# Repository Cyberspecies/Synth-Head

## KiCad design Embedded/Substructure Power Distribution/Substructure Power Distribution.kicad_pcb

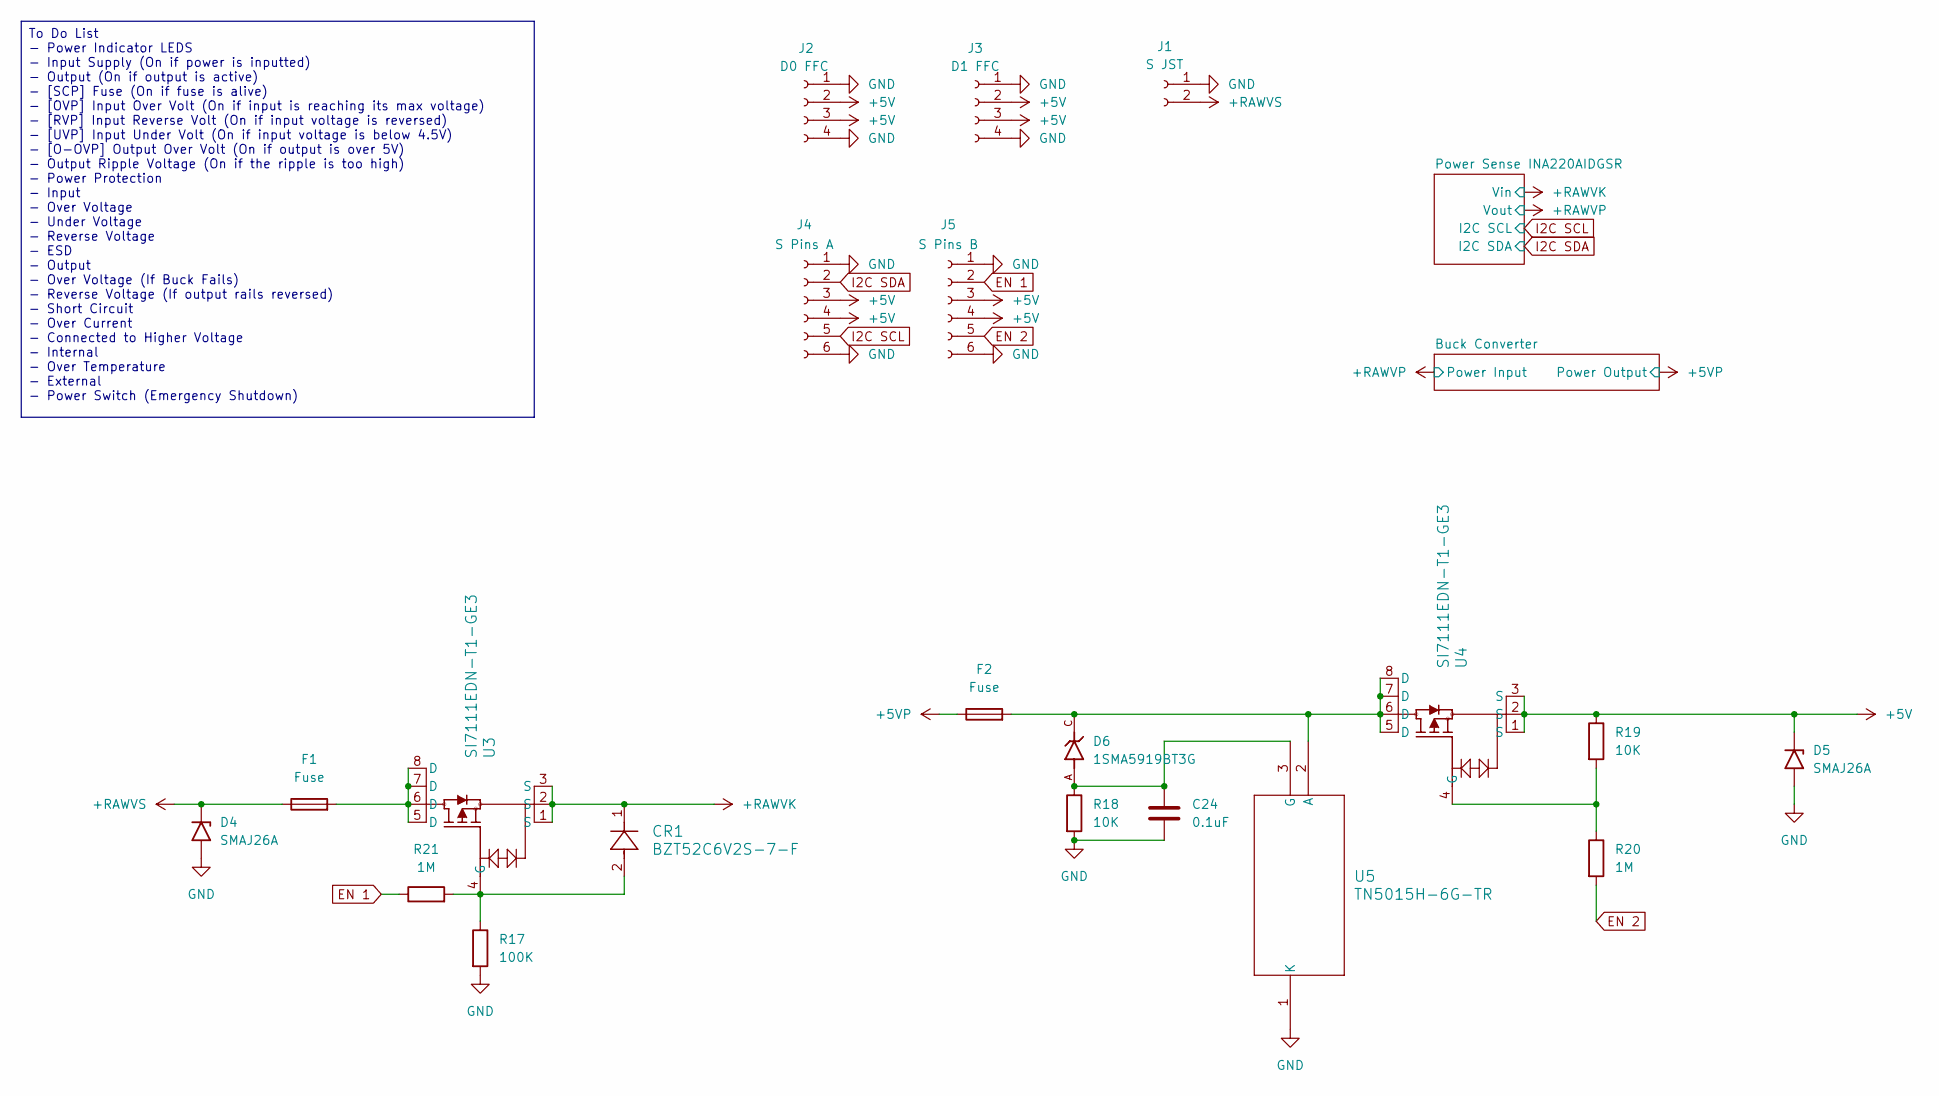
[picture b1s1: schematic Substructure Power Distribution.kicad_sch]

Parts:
C24: 0.1uF; C_0603_1608Metric_Pad1.08x0.95mm_HandSolder
CR1: BZT52C6V2S-7-F; SOD323_DIO
D4, D5: SMAJ26A; D_SMA
D6: 1SMA5919BT3G; DIOM5226X220N; PARTREV 10
F1, F2: Fuse; Fuse_1206_3216Metric_Pad1.42x1.75mm_HandSolder; LCSC C126815
J1: S JST; AMASS_XT30PW-M_1x02_P2.50mm_Horizontal
J2: D0 FFC; JST_XH_B4B-XH-A_1x04_P2.50mm_Vertical
J3: D1 FFC; JST_XH_B4B-XH-A_1x04_P2.50mm_Vertical
J4: S Pins A; PinHeader_1x06_P2.54mm_Vertical
J5: S Pins B; PinHeader_1x06_P2.54mm_Vertical
R17: 100K; R_0603_1608Metric_Pad0.98x0.95mm_HandSolder
R18, R19: 10K; R_0603_1608Metric_Pad0.98x0.95mm_HandSolder
R20, R21: 1M; R_0603_1608Metric_Pad0.98x0.95mm_HandSolder
U3, U4: SI7111EDN-T1-GE3; MOSFET_0DN-T1-GE3_VIS
U5: TN5015H-6G-TR; D2PAK_T2550_STM-M

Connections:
+5V: D5.1 (A1), J2.2, J2.3, J3.2, J3.3, J4.3, J4.4, J5.3, J5.4, R19.1, U4.1 (S), U4.2 (S), U4.3 (S)
+5VP: F2.1; also elsewhere on the board
+RAWVK: CR1.1, U3.1 (S), U3.2 (S), U3.3 (S); also elsewhere on the board
+RAWVS: D4.1 (A1), F1.1, J1.2
EN 1: J5.2, R21.1
EN 2: J5.5, R20.2
GND: C24.2, D4.2 (A2), D5.2 (A2), J1.1, J2.1, J2.4, J3.1, J3.4, J4.1, J4.6, J5.1, J5.6, R17.2, R18.2, U5.1 (K); also elsewhere on the board
I2C SCL: J4.5; also elsewhere on the board
I2C SDA: J4.2; also elsewhere on the board
unnamed: F1.2, U3.5 (D), U3.6 (D), U3.7 (D), U3.8 (D)
unnamed: CR1.2, R17.1, R21.2, U3.4 (G)
unnamed: R19.2, R20.1, U4.4 (G)
unnamed: D6.C, F2.2, U4.5 (D), U4.6 (D), U4.7 (D), U4.8 (D), U5.2 (A)
unnamed: C24.1, D6.A, R18.1, U5.3 (G)

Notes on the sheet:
To Do List - Power Indicator LEDS - Input Supply (On if power is inputted) - Output (On if output is active) - [SCP] Fuse (On if fuse is alive) - [OVP] Input Over Volt (On if input is reaching its max voltage) - [RVP] Input Reverse Volt (On if input voltage is reversed) - [UVP] Input Under Volt (On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

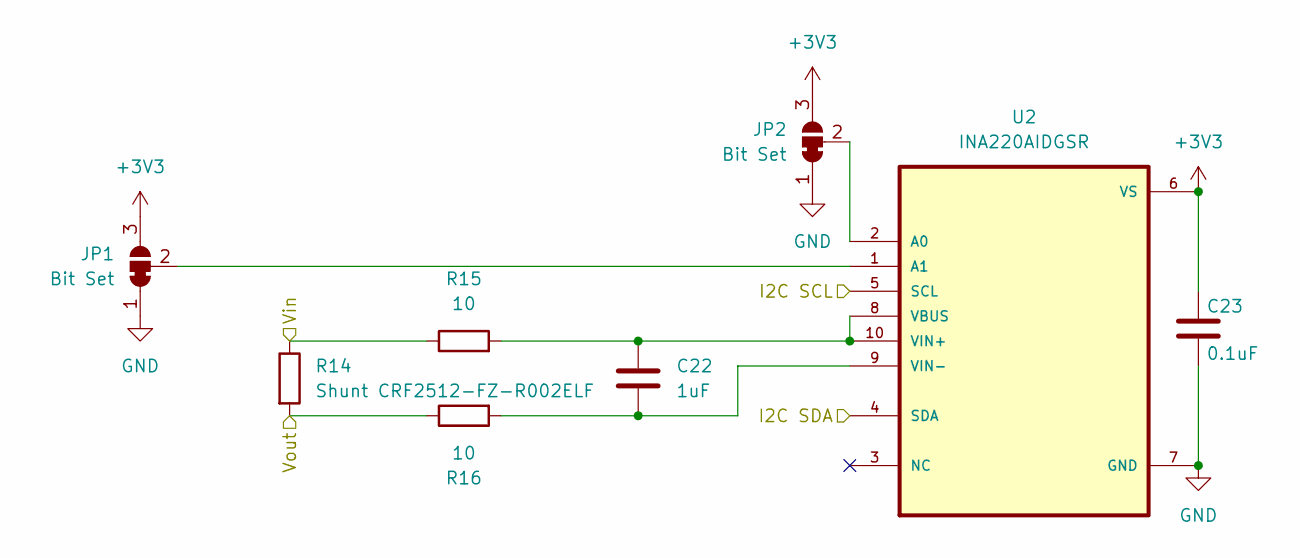
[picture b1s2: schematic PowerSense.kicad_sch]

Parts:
C22: 1uF; C_0402_1005Metric_Pad0.74x0.62mm_HandSolder
C23: 0.1uF; C_0402_1005Metric_Pad0.74x0.62mm_HandSolder
JP1, JP2: Bit Set; SolderJumper-3_P1.3mm_Bridged2Bar12_RoundedPad1.0x1.5mm
R14: Shunt CRF2512-FZ-R002ELF; R_2512_6332Metric_Pad1.40x3.35mm_HandSolder
R15, R16: 10; R_0402_1005Metric_Pad0.72x0.64mm_HandSolder
U2: INA220AIDGSR; SOP50P490X110-10N

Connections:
+3V3: C23.1, JP1.3 (B), JP2.3 (B), U2.6 (VS)
+RAWVK: R14.1, R15.1; also elsewhere on the board
+RAWVP: R14.2, R16.1; also elsewhere on the board
GND: C23.2, JP1.1 (A), JP2.1 (A), U2.7 (GND); also elsewhere on the board
I2C SCL: U2.5 (SCL); also elsewhere on the board
I2C SDA: U2.4 (SDA); also elsewhere on the board
unnamed: JP1.2 (C), U2.1 (A1)
unnamed: JP2.2 (C), U2.2 (A0)
unnamed: C22.1, R15.2, U2.8 (VBUS), U2.10 (VIN+)
unnamed: C22.2, R16.2, U2.9 (VIN-)

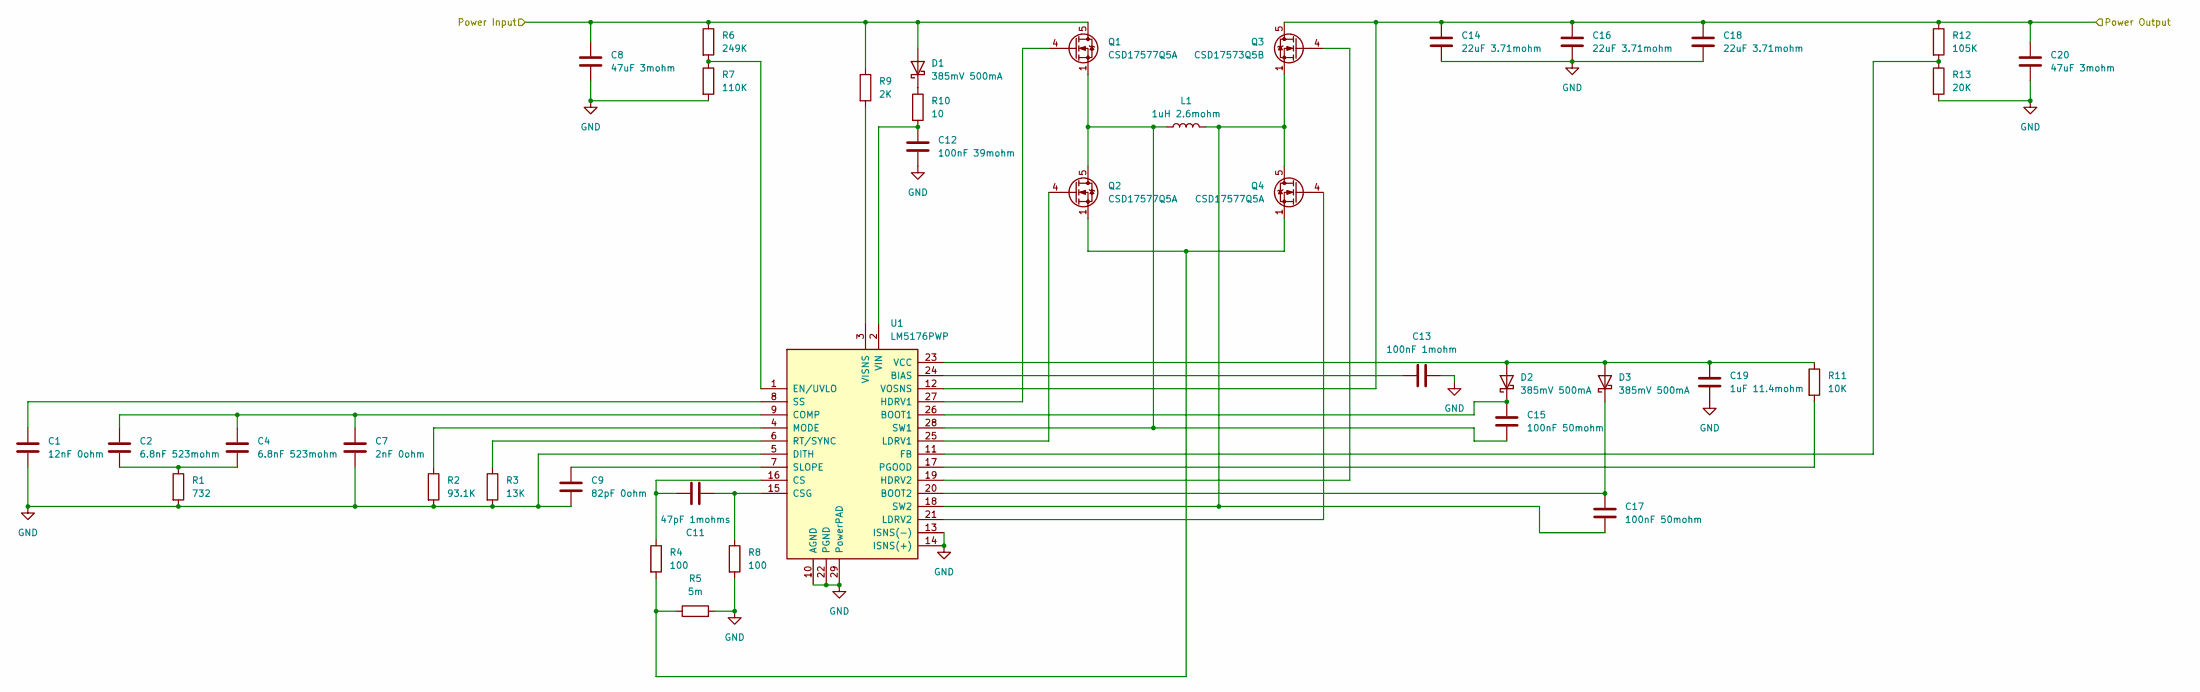
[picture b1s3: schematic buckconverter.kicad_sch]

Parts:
C1: 12nF 0ohm; C_0603_1608Metric_Pad1.08x0.95mm_HandSolder; LCSC C519540
C2, C4: 6.8nF 523mohm; C_0402_1005Metric_Pad0.74x0.62mm_HandSolder; LCSC C3840335
C7: 2nF 0ohm; C_0402_1005Metric_Pad0.74x0.62mm_HandSolder; LCSC C1845704
C8, C20: 47uF 3mohm; C_1210_3225Metric_Pad1.33x2.70mm_HandSolder; LCSC C77101
C9: 82pF 0ohm; C_0402_1005Metric_Pad0.74x0.62mm_HandSolder; LCSC C650992
C11: 47pF 1mohms; C_0402_1005Metric_Pad0.74x0.62mm_HandSolder; LCSC C76970
C12: 100nF 39mohm; R_0402_1005Metric_Pad0.72x0.64mm_HandSolder; LCSC C2181865
C13: 100nF 1mohm; C_0402_1005Metric_Pad0.74x0.62mm_HandSolder; LCSC C133086
C14, C16, C18: 22uF 3.71mohm; C_0603_1608Metric_Pad1.08x0.95mm_HandSolder; LCSC C86295
C15, C17: 100nF 50mohm; C_0603_1608Metric_Pad1.08x0.95mm_HandSolder; LCSC C92490
C19: 1uF 11.4mohm; C_0402_1005Metric_Pad0.74x0.62mm_HandSolder; LCSC C181015
D1: 385mV 500mA; D_SOD-123; LCSC C155367
D2, D3: 385mV 500mA; D_SOD-123; LCSC C398783
L1: 1uH 2.6mohm; XAL7070-102ME; LCSC C6609502
Q1, Q2, Q4: CSD17577Q5A; TDSON-8-1; LCSC C475504
Q3: CSD17573Q5B; TDSON-8-1; LCSC C202231
R1: 732; R_0402_1005Metric_Pad0.72x0.64mm_HandSolder; LCSC C2085222
R2: 93.1K; R_0402_1005Metric_Pad0.72x0.64mm_HandSolder; LCSC C2085865
R3: 13K; R_0402_1005Metric_Pad0.72x0.64mm_HandSolder; LCSC C294438
R4, R8: 100; R_0402_1005Metric_Pad0.72x0.64mm_HandSolder; LCSC C844713
R5: 5m; R_2512_6332Metric_Pad1.40x3.35mm_HandSolder; LCSC C22468851
R6: 249K; C_0402_1005Metric_Pad0.74x0.62mm_HandSolder; LCSC C482111
R7: 110K; C_0402_1005Metric_Pad0.74x0.62mm_HandSolder; LCSC C481928
R9: 2K; C_0402_1005Metric_Pad0.74x0.62mm_HandSolder; LCSC C482125
R10: 10; R_0402_1005Metric_Pad0.72x0.64mm_HandSolder; LCSC C481926
R11: 10K; R_0402_1005Metric_Pad0.72x0.64mm_HandSolder; LCSC C71617
R12: 105K; R_0603_1608Metric_Pad0.98x0.95mm_HandSolder; LCSC C227540
R13: 20K; R_0603_1608Metric_Pad0.98x0.95mm_HandSolder; LCSC C105575
U1: LM5176PWP; HTSSOP-28-1EP_4.4x9.7mm_P0.65mm_EP3.4x9.5mm_ThermalVias

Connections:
+5VP: C14.1, C16.1, C18.1, C20.1, Q3.5 (D), R12.1, U1.12 (VOSNS); also elsewhere on the board
+RAWVP: C8.1, D1.2 (A), Q1.5 (D), R6.1, R9.1; also elsewhere on the board
GND: C1.2, C7.2, C8.2, C9.2, C12.2, C13.2, C14.2, C16.2, C18.2, C19.2, C20.2, R1.2, R2.2, R3.2, R5.2, R7.2, R8.2, R13.2, U1.5 (DITH), U1.10 (AGND), U1.13 (ISNS(-)), U1.14 (ISNS(+)), U1.22 (PGND), U1.29 (PowerPAD); also elsewhere on the board
unnamed: C2.2, C4.2, R1.1
unnamed: D1.1 (K), R10.1
unnamed: C19.1, D2.2 (A), D3.2 (A), R11.1, U1.23 (VCC)
unnamed: C15.1, D2.1 (K), U1.26 (BOOT1)
unnamed: C17.1, D3.1 (K), U1.20 (BOOT2)
unnamed: Q1.4 (G), U1.27 (HDRV1)
unnamed: C15.2, L1.1, Q1.1 (S), Q1.2 (S), Q1.3 (S), Q2.5 (D), U1.28 (SW1)
unnamed: Q2.4 (G), U1.25 (LDRV1)
unnamed: Q2.1 (S), Q2.2 (S), Q2.3 (S), Q4.1 (S), Q4.2 (S), Q4.3 (S), R4.2, R5.1
unnamed: Q3.4 (G), U1.19 (HDRV2)
unnamed: C17.2, L1.2, Q3.1 (S), Q3.2 (S), Q3.3 (S), Q4.5 (D), U1.18 (SW2)
unnamed: Q4.4 (G), U1.21 (LDRV2)
unnamed: C13.1, U1.24 (BIAS)
unnamed: C2.1, C4.1, C7.1, U1.9 (COMP)
unnamed: C11.1, R4.1, U1.16 (CS)
unnamed: C11.2, R8.1, U1.15 (CSG)
unnamed: R6.2, R7.1, U1.1 (EN/UVLO)
unnamed: R12.2, R13.1, U1.11 (FB)
unnamed: R2.1, U1.4 (MODE)
unnamed: R11.2, U1.17 (PGOOD)
unnamed: R3.1, U1.6 (RT/SYNC)
unnamed: C9.1, U1.7 (SLOPE)
unnamed: C1.1, U1.8 (SS)
unnamed: C12.1, R10.2, U1.2 (VIN)
unnamed: R9.2, U1.3 (VISNS)

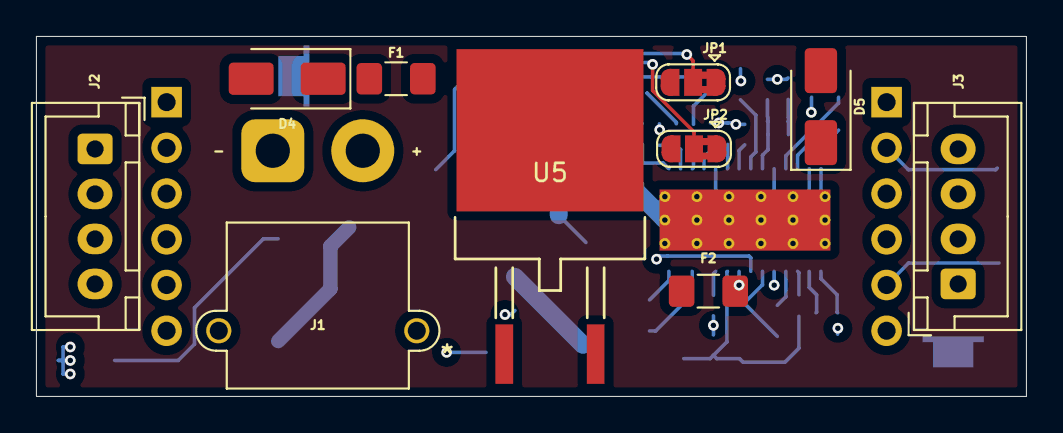
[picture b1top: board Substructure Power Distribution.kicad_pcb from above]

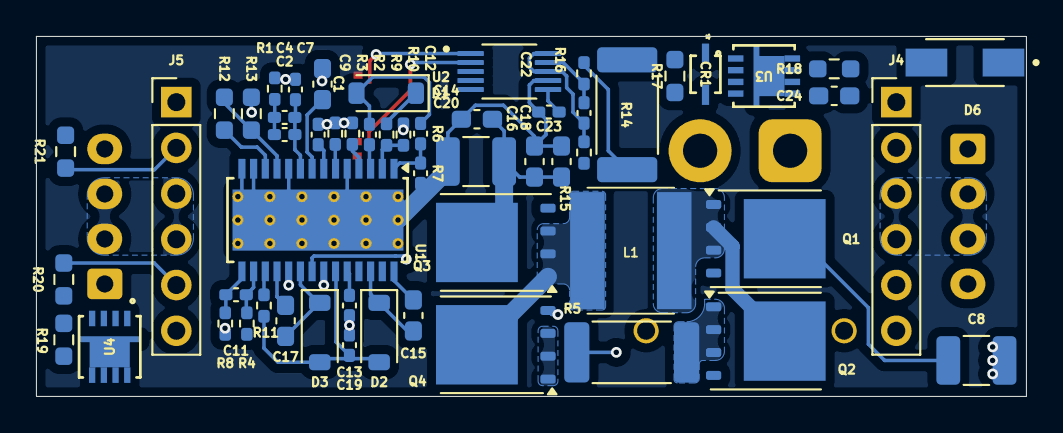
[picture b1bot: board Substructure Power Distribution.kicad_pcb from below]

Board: 4 copper layers, 55.0 x 20.0 mm, 66 parts (56 on the bottom side), 45 nets.

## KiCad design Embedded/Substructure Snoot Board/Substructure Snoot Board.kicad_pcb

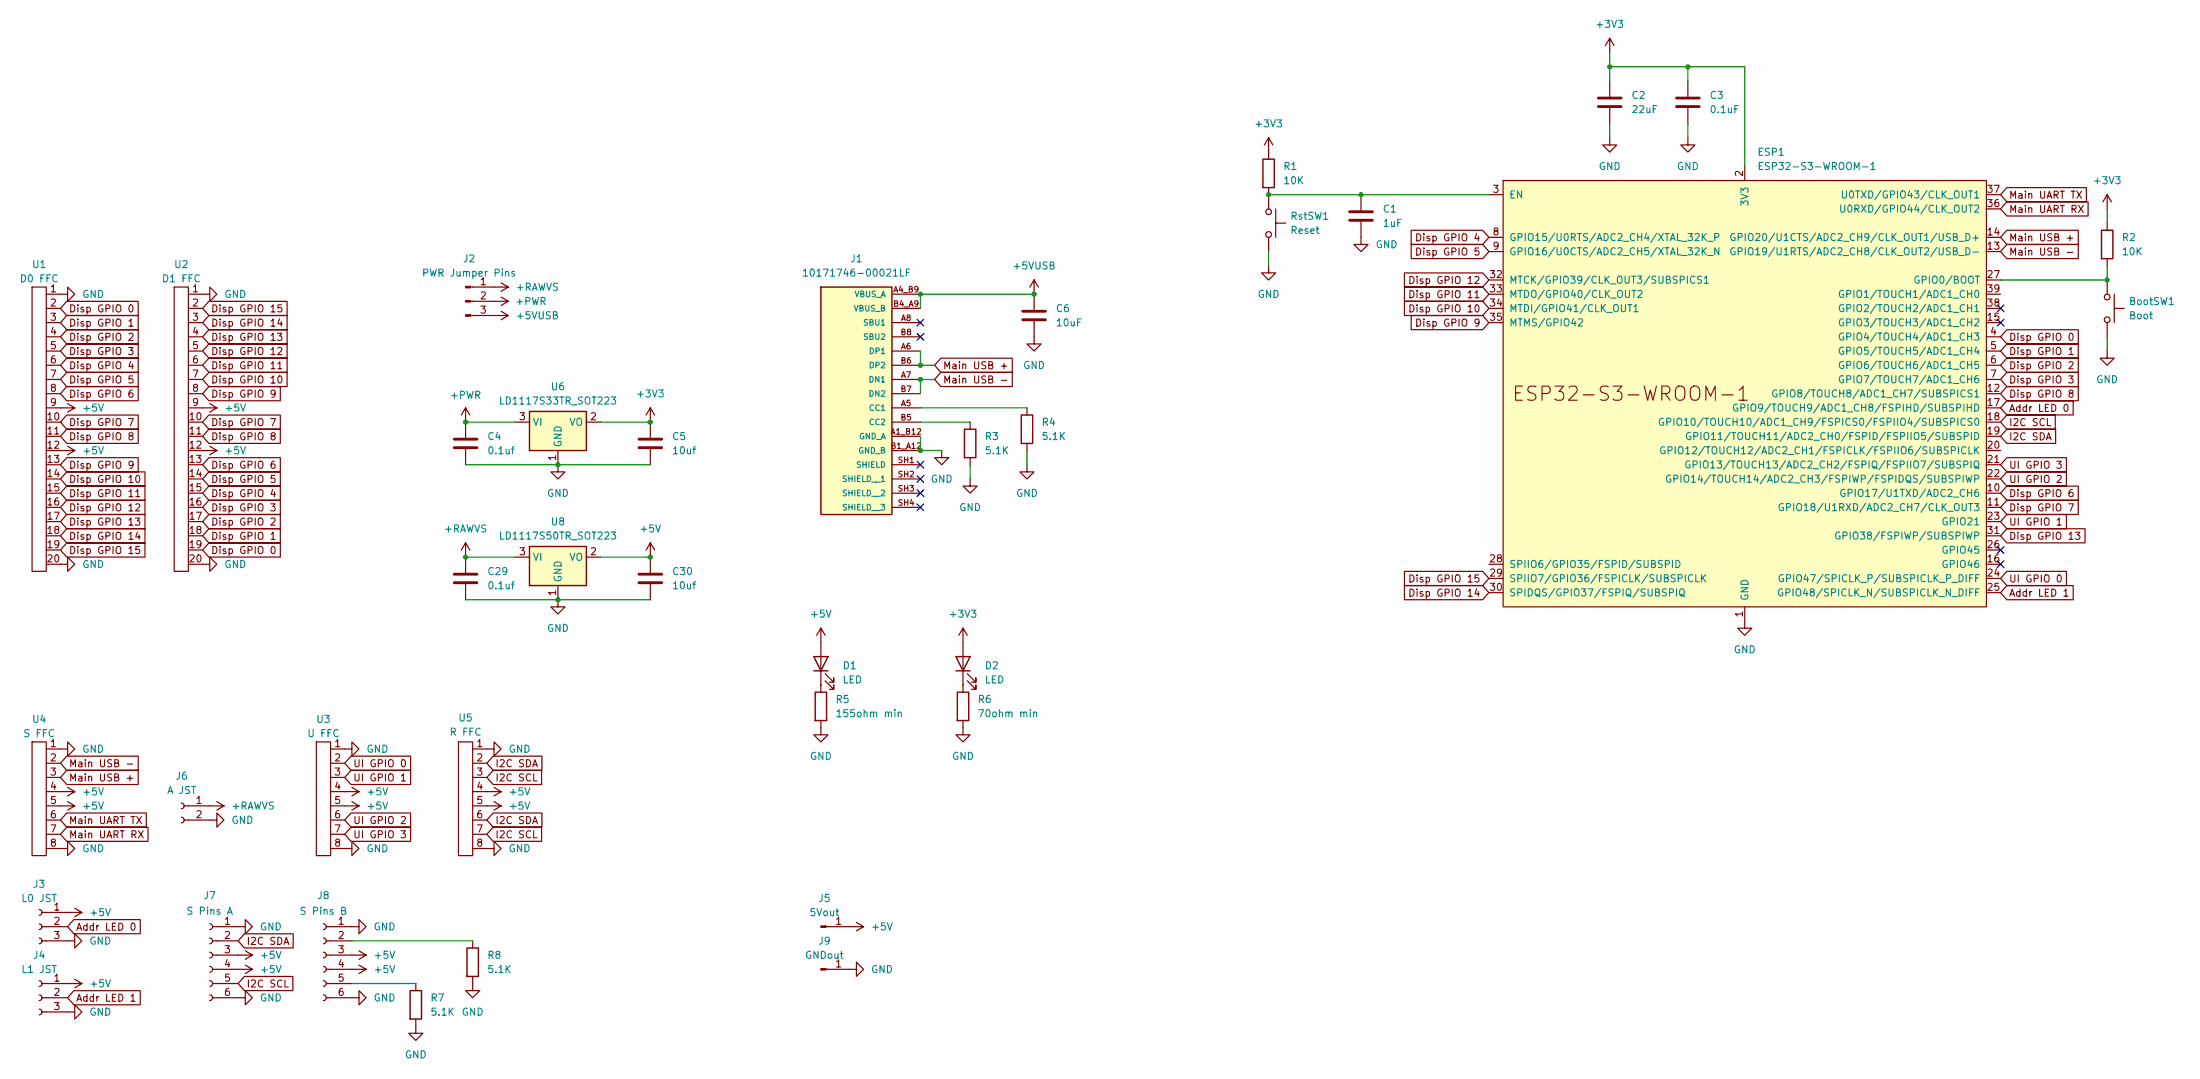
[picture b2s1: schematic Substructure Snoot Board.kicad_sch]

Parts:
BootSW1: Boot; R-667843
C1: 1uF; C_0603_1608Metric
C2: 22uF; C_0603_1608Metric_Pad1.08x0.95mm_HandSolder
C3: 0.1uF; C_0603_1608Metric_Pad1.08x0.95mm_HandSolder
C4: 0.1uf; C_0402_1005Metric_Pad0.74x0.62mm_HandSolder; LCSC C155422
C5: 10uf; C_0402_1005Metric_Pad0.74x0.62mm_HandSolder; LCSC C408132
C6: 10uF; C_0603_1608Metric
C29: 0.1uf; C_0402_1005Metric_Pad0.74x0.62mm_HandSolder
C30: 10uf; C_0402_1005Metric_Pad0.74x0.62mm_HandSolder
D1, D2: LED; D_0603_1608Metric_Pad1.05x0.95mm_HandSolder
ESP1: ESP32-S3-WROOM-1; ESP32-S3-WROOM-1U
J1: 10171746-00021LF; AMPHENOL_10171746-00021LF; PARTREV A
J2: PWR Jumper Pins; PinHeader_1x03_P2.54mm_Horizontal
J3: L0 JST; JST_GH_SM03B-GHS-TB_1x03-1MP_P1.25mm_Horizontal
J4: L1 JST; JST_GH_SM03B-GHS-TB_1x03-1MP_P1.25mm_Horizontal
J5: 5Vout; TestPoint_Pad_D4.0mm
J6: A JST; JST_GH_SM02B-GHS-TB_1x02-1MP_P1.25mm_Horizontal
J7: S Pins A; PinSocket_1x06_P2.54mm_Vertical
J8: S Pins B; PinSocket_1x06_P2.54mm_Vertical
J9: GNDout; TestPoint_Pad_D4.0mm
R1, R2: 10K; R_0603_1608Metric
R3, R4, R7, R8: 5.1K; R_0603_1608Metric
R5: 155ohm min; R_0402_1005Metric_Pad0.72x0.64mm_HandSolder
R6: 70ohm min; R_0402_1005Metric_Pad0.72x0.64mm_HandSolder
RstSW1: Reset; R-667843
U1: D0 FFC; FFC-20-0.5
U2: D1 FFC; FFC-20-0.5
U3: U FFC; FFC-8-0.5
U4: S FFC; FFC-8-0.5
U5: R FFC; FFC-8-0.5
U6: LD1117S33TR_SOT223; SOT-223-3_TabPin2; LCSC C86781
U8: LD1117S50TR_SOT223; SOT-223-3_TabPin2

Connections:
+3V3: C2.1, C3.1, C5.1, D2.2 (A), ESP1.2 (3V3), R1.1, R2.1, U6.2 (VO)
+5V: C30.1, D1.2 (A), J3.1, J4.1, J5.1, J7.3, J7.4, J8.3, J8.4, U1.9, U1.12, U2.9, U2.12, U3.4, U3.5, U4.4, U4.5, U5.4, U5.5, U8.2 (VO)
+5VUSB: C6.1, J1.A4_B9 (VBUS_A), J1.B4_A9 (VBUS_B), J2.3
+PWR: C4.1, J2.2, U6.3 (VI)
+RAWVS: C29.1, J2.1, J6.1, U8.3 (VI)
Addr LED 0: ESP1.17 (GPIO9/TOUCH9/ADC1_CH8/FSPIHD/SUBSPIHD), J3.2
Addr LED 1: ESP1.25 (GPIO48/SPICLK_N/SUBSPICLK_N_DIFF), J4.2
Disp GPIO 0: ESP1.4 (GPIO4/TOUCH4/ADC1_CH3), U1.2, U2.19
Disp GPIO 1: ESP1.5 (GPIO5/TOUCH5/ADC1_CH4), U1.3, U2.18
Disp GPIO 2: ESP1.6 (GPIO6/TOUCH6/ADC1_CH5), U1.4, U2.17
Disp GPIO 3: ESP1.7 (GPIO7/TOUCH7/ADC1_CH6), U1.5, U2.16
Disp GPIO 4: ESP1.8 (GPIO15/U0RTS/ADC2_CH4/XTAL_32K_P), U1.6, U2.15
Disp GPIO 5: ESP1.9 (GPIO16/U0CTS/ADC2_CH5/XTAL_32K_N), U1.7, U2.14
Disp GPIO 6: ESP1.10 (GPIO17/U1TXD/ADC2_CH6), U1.8, U2.13
Disp GPIO 7: ESP1.11 (GPIO18/U1RXD/ADC2_CH7/CLK_OUT3), U1.10, U2.10
Disp GPIO 8: ESP1.12 (GPIO8/TOUCH8/ADC1_CH7/SUBSPICS1), U1.11, U2.11
Disp GPIO 9: ESP1.35 (MTMS/GPIO42), U1.13, U2.8
Disp GPIO 10: ESP1.34 (MTDI/GPIO41/CLK_OUT1), U1.14, U2.7
Disp GPIO 11: ESP1.33 (MTDO/GPIO40/CLK_OUT2), U1.15, U2.6
Disp GPIO 12: ESP1.32 (MTCK/GPIO39/CLK_OUT3/SUBSPICS1), U1.16, U2.5
Disp GPIO 13: ESP1.31 (GPIO38/FSPIWP/SUBSPIWP), U1.17, U2.4
Disp GPIO 14: ESP1.30 (SPIDQS/GPIO37/FSPIQ/SUBSPIQ), U1.18, U2.3
Disp GPIO 15: ESP1.29 (SPIIO7/GPIO36/FSPICLK/SUBSPICLK), U1.19, U2.2
GND: BootSW1.2, C1.1, C2.2, C3.2, C4.2, C5.2, C6.2, C29.2, C30.2, ESP1.1 (GND), ESP1.40 (GND), ESP1.41 (GND), J1.A1_B12 (GND_A), J1.B1_A12 (GND_B), J3.3, J4.3, J6.2, J7.1, J7.6, J8.1, J8.6, J9.1, R3.2, R4.2, R5.2, R6.2, R7.2, R8.2, RstSW1.2, U1.1, U1.20, U2.1, U2.20, U3.1, U3.8, U4.1, U4.8, U5.1, U5.8, U6.1 (GND), U8.1 (GND)
I2C SCL: ESP1.18 (GPIO10/TOUCH10/ADC1_CH9/FSPICS0/FSPIIO4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), J7.5, U5.3, U5.7
I2C SDA: ESP1.19 (GPIO11/TOUCH11/ADC2_CH0/FSPID/FSPIIO5/S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), J7.2, U5.2, U5.6
Main UART RX: ESP1.36 (U0RXD/GPIO44/CLK_OUT2), U4.7
Main UART TX: ESP1.37 (U0TXD/GPIO43/CLK_OUT1), U4.6
Main USB +: ESP1.14 (GPIO20/U1CTS/ADC2_CH9/CLK_OUT1/USB_D+), J1.A6 (DP1), J1.B6 (DP2), U4.3
Main USB -: ESP1.13 (GPIO19/U1RTS/ADC2_CH8/CLK_OUT2/USB_D-), J1.A7 (DN1), J1.B7 (DN2), U4.2
unnamed: D1.1 (K), R5.1
unnamed: D2.1 (K), R6.1
unnamed: C1.2, ESP1.3 (EN), R1.2, RstSW1.1
unnamed: BootSW1.1, ESP1.27 (GPIO0/BOOT), R2.2
unnamed: J1.A5 (CC1), R4.1
unnamed: J1.B5 (CC2), R3.1
unnamed: J8.2, R8.1
unnamed: J8.5, R7.1
UI GPIO 0: ESP1.24 (GPIO47/SPICLK_P/SUBSPICLK_P_DIFF), U3.2
UI GPIO 1: ESP1.23 (GPIO21), U3.3
UI GPIO 2: ESP1.22 (GPIO14/TOUCH14/ADC2_CH3/FSPIWP/FSPIDQS/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), U3.6
UI GPIO 3: ESP1.21 (GPIO13/TOUCH13/ADC2_CH2/FSPIQ/FSPIIO7/S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), U3.7

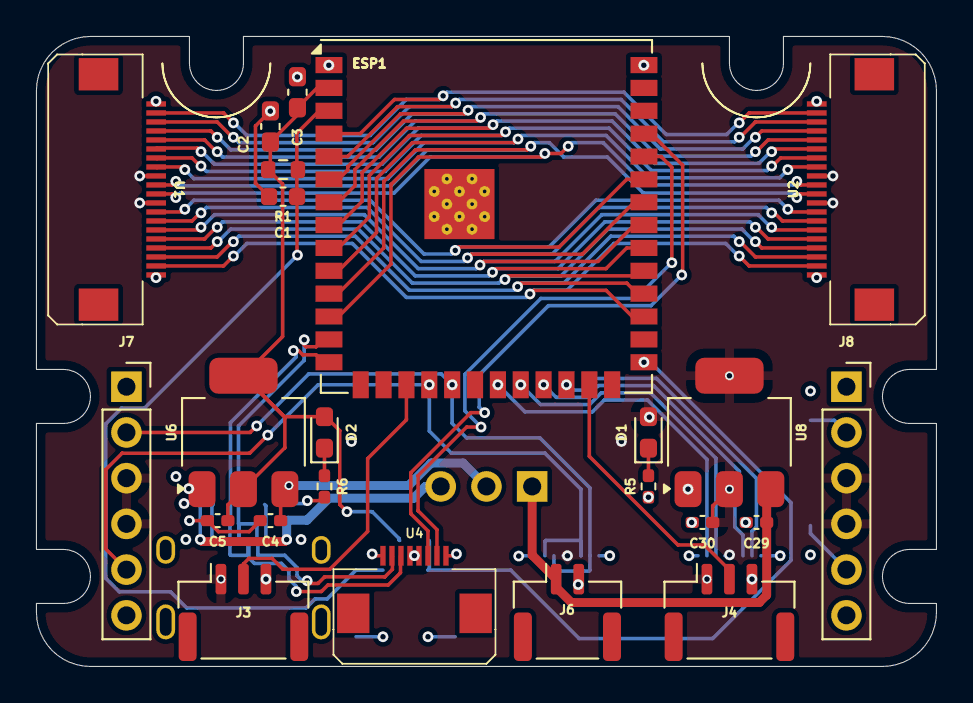
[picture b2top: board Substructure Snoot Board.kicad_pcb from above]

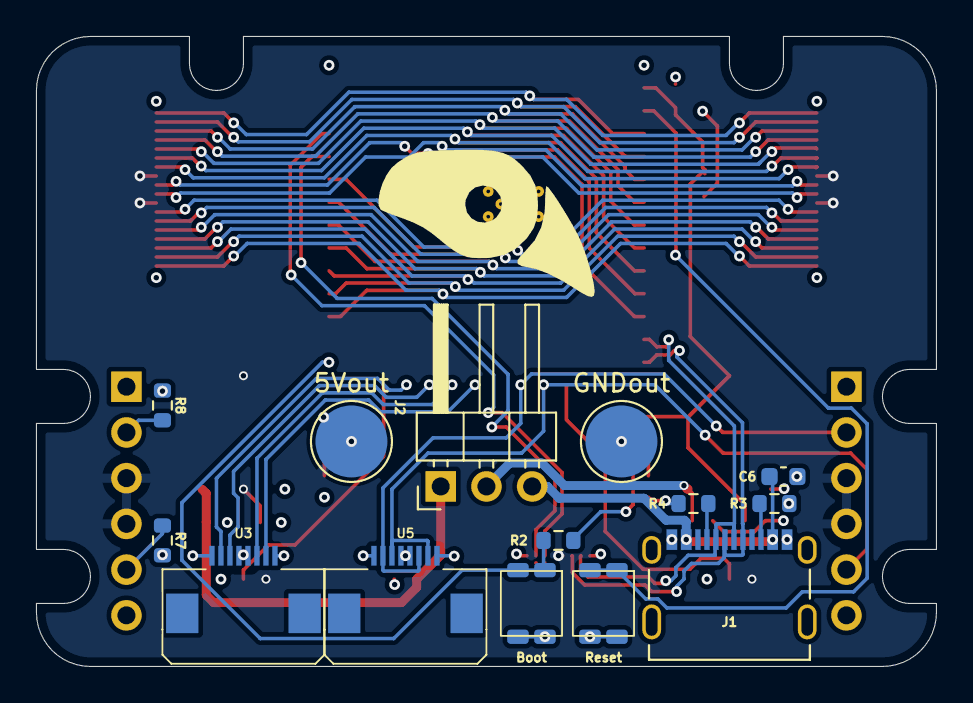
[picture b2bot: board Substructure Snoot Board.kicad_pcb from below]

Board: 4 copper layers, 50.0 x 35.0 mm, 37 parts (14 on the bottom side), 42 nets.

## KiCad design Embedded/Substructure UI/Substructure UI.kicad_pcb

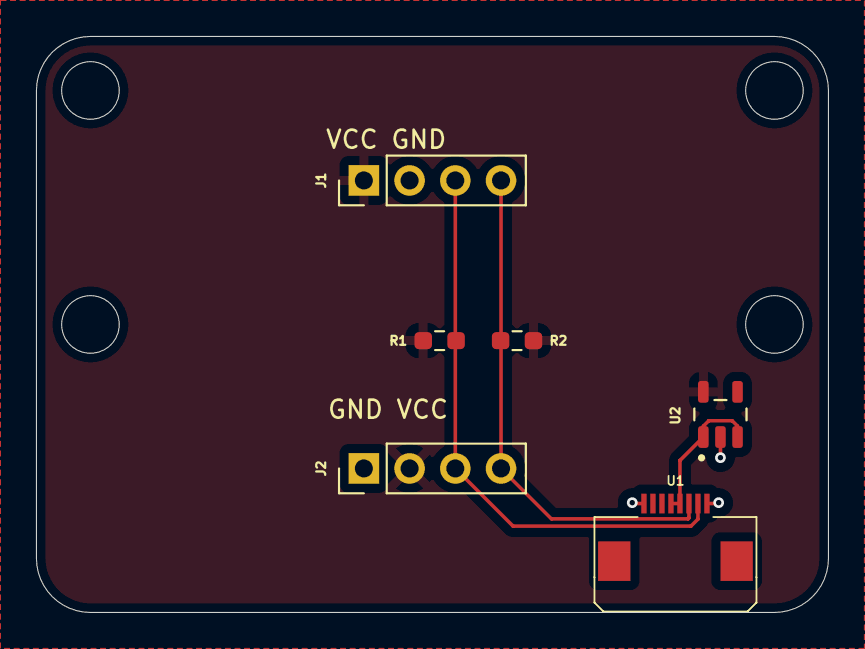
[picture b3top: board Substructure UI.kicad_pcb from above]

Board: 2 copper layers, 44.0 x 32.0 mm, 6 parts (0 on the bottom side), 5 nets.

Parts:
J1, J2: Conn_01x04_Socket; PinHeader_1x04_P2.54mm_Vertical
R1, R2: 10Kohms; R_0603_1608Metric_Pad0.98x0.95mm_HandSolder
U1: FFC 0.8mm 8P
U2: TLV74133PDBVR; SOT95P280X145-5N

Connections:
+3V3: J1.1, J2.2, R1.1, R2.1, U2.5 (OUT)
+5V: U1.4, U1.5, U2.1 (IN), U2.3 (EN)
GND: J1.2, J2.1, U1.1, U1.8, U2.2 (GND)
GPIO 0: J1.3, J2.3, R1.2, U1.7
GPIO 1: J1.4, J2.4, R2.2, U1.6

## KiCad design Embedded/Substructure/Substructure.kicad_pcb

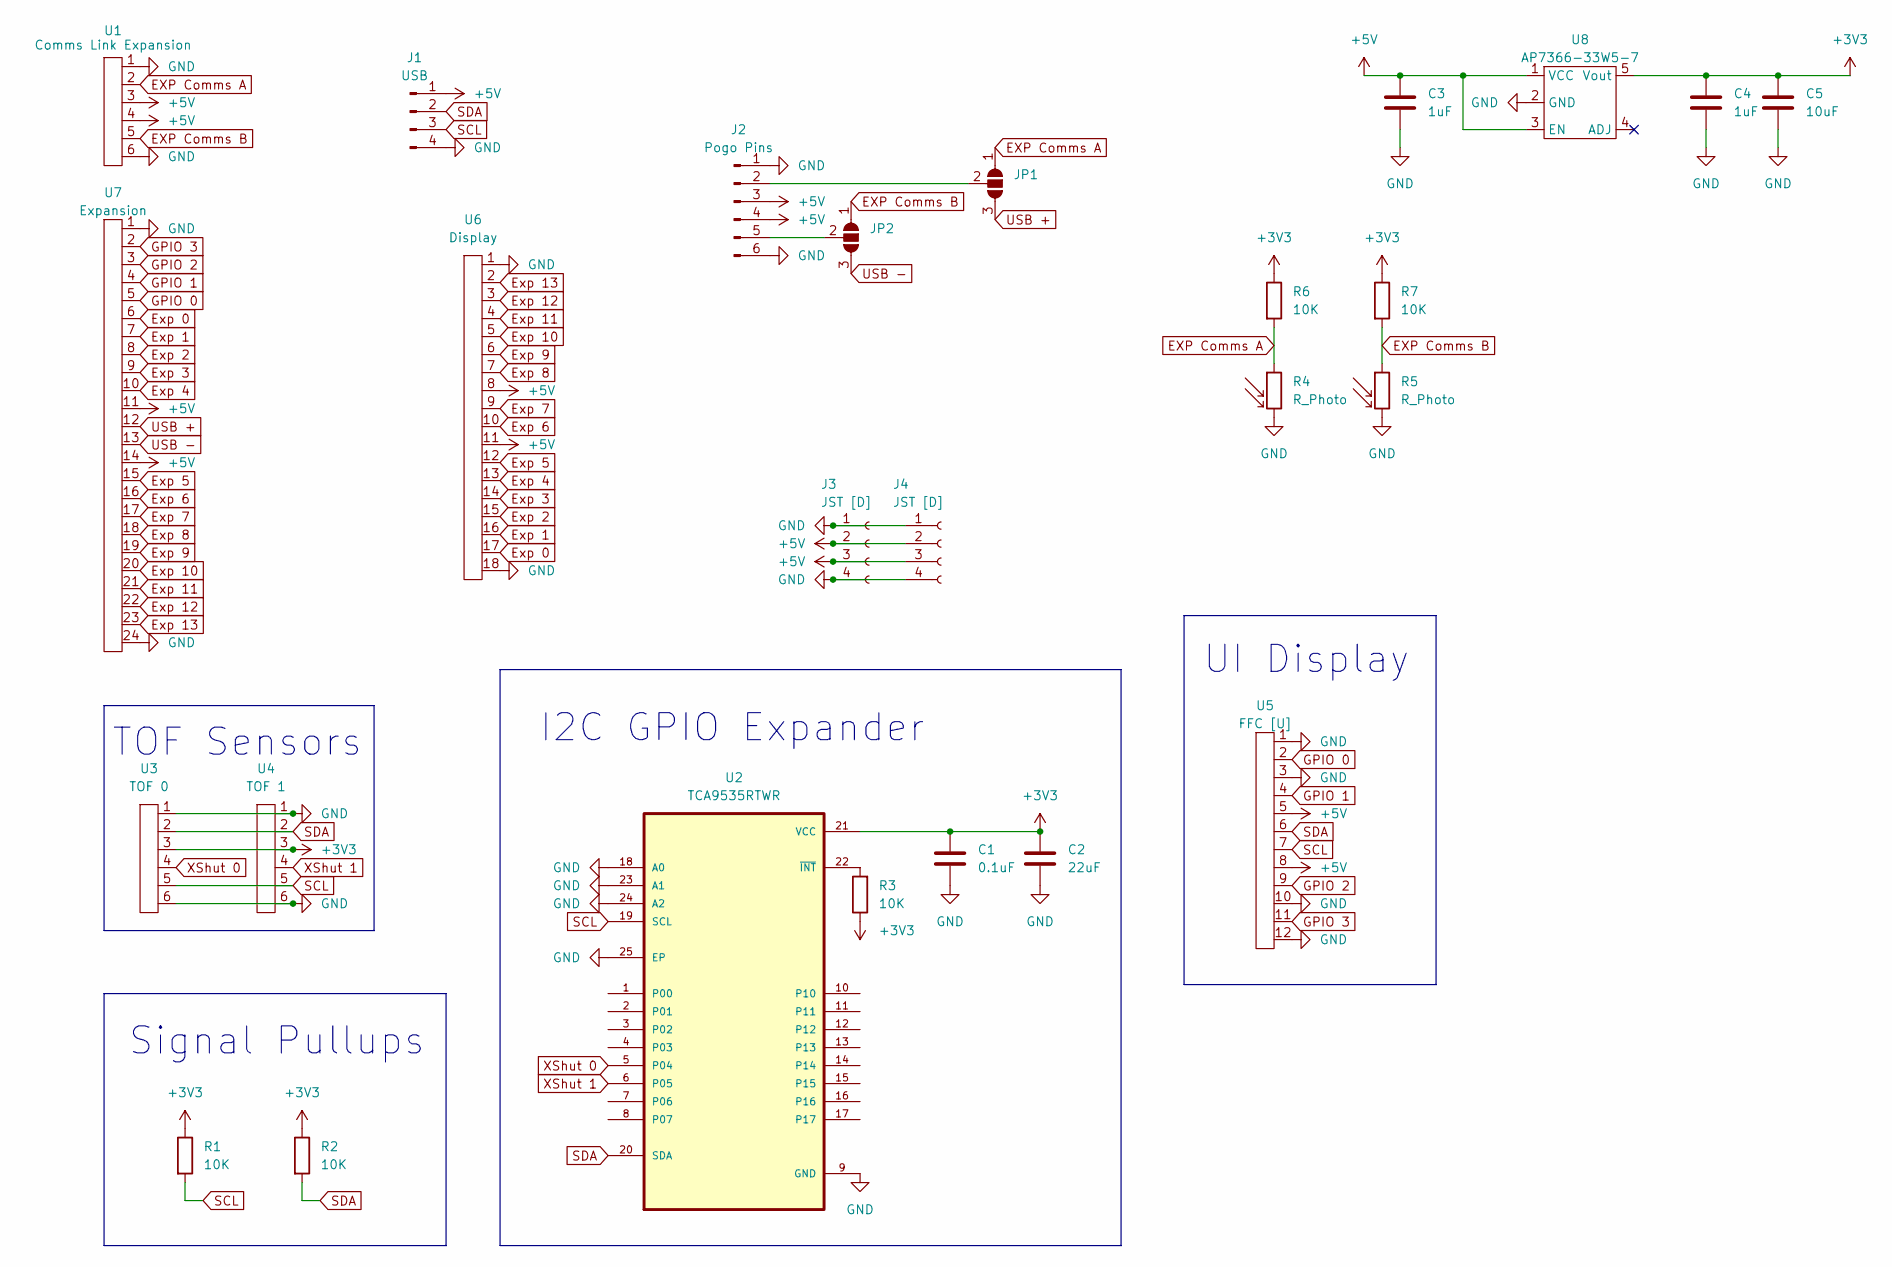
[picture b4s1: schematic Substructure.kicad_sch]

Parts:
C1: 0.1uF; C_0603_1608Metric
C2: 22uF; C_0603_1608Metric_Pad1.08x0.95mm_HandSolder
C3, C4: 1uF; R_0603_1608Metric
C5: 10uF; C_0603_1608Metric
J1: USB; Hirose_DF13-04P-1.25DS_1x04_P1.25mm_Horizontal
J2: Pogo Pins; PinHeader_1x06_P2.54mm_Vertical
J3, J4: JST [D]; Molex_PicoBlade_53048-0410_1x04_P1.25mm_Horizontal
JP1, JP2: SolderJumper_3_Open; SolderJumper-3_P1.3mm_Open_RoundedPad1.0x1.5mm
R1, R2, R6, R7: 10K; R_0603_1608Metric_Pad0.98x0.95mm_HandSolder
R3: 10K; R_0603_1608Metric
R4, R5: R_Photo; Photoresistor Aliexpress
U1: Comms Link Expansion; FFC Aliexpress 0.5mm 6P
U2: TCA9535RTWR; QFN50P400X400X80-25N
U3: TOF 0; Hirose_DF13-06P-1.25DS_1x06_P1.25mm_Horizontal
U4: TOF 1; Hirose_DF13-06P-1.25DS_1x06_P1.25mm_Horizontal
U5: FFC [U]; FFC Aliexpress 0.5mm 12P
U6: Display; FFC Aliexpress 0.5mm 18P
U7: Expansion; FFC Aliexpress 0.5mm 24P
U8: AP7366-33W5-7; AP7366

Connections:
+3V3: C1.1, C2.1, C4.1, C5.1, R1.1, R2.1, R3.1, R6.1, R7.1, U2.21 (VCC), U3.3, U4.3, U8.5 (Vout)
+5V: C3.1, J1.1, J2.3, J2.4, J3.2, J3.3, J4.2, J4.3, U1.3, U1.4, U5.5, U5.8, U6.8, U6.11, U7.11, U7.14, U8.1 (VCC), U8.3 (EN)
EXP Comms A: JP1.1 (A), R4.1, R6.2, U1.2
EXP Comms B: JP2.1 (A), R5.1, R7.2, U1.5
Exp 0: U6.17, U7.6
Exp 1: U6.16, U7.7
Exp 2: U6.15, U7.8
Exp 3: U6.14, U7.9
Exp 4: U6.13, U7.10
Exp 5: U6.12, U7.15
Exp 6: U6.10, U7.16
Exp 7: U6.9, U7.17
Exp 8: U6.7, U7.18
Exp 9: U6.6, U7.19
Exp 10: U6.5, U7.20
Exp 11: U6.4, U7.21
Exp 12: U6.3, U7.22
Exp 13: U6.2, U7.23
GND: C1.2, C2.2, C3.2, C4.2, C5.2, J1.4, J2.1, J2.6, J3.1, J3.4, J4.1, J4.4, R4.2, R5.2, U1.1, U1.6, U2.9 (GND), U2.18 (A0), U2.23 (A1), U2.24 (A2), U2.25 (EP), U3.1, U3.6, U4.1, U4.6, U5.1, U5.3, U5.10, U5.12, U6.1, U6.18, U7.1, U7.24, U8.2 (GND)
GPIO 0: U5.2, U7.5
GPIO 1: U5.4, U7.4
GPIO 2: U5.9, U7.3
GPIO 3: U5.11, U7.2
unnamed: J2.2, JP1.2 (C)
unnamed: J2.5, JP2.2 (C)
unnamed: R3.2, U2.22 (~INT)
SCL: J1.3, R1.2, U2.19 (SCL), U3.5, U4.5, U5.7
SDA: J1.2, R2.2, U2.20 (SDA), U3.2, U4.2, U5.6
USB +: JP1.3 (B), U7.12
USB -: JP2.3 (B), U7.13
XShut 0: U2.5 (P04), U3.4
XShut 1: U2.6 (P05), U4.4

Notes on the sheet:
Signal Pullups
UI Display
I2C GPIO Expander
TOF Sensors

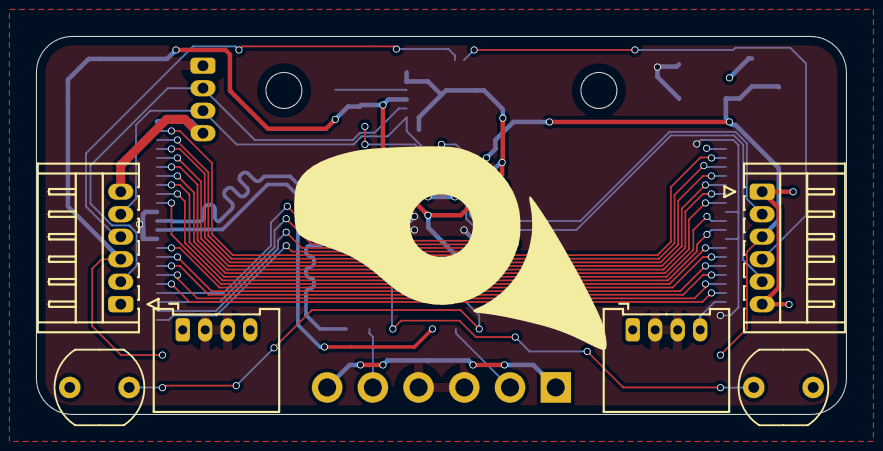
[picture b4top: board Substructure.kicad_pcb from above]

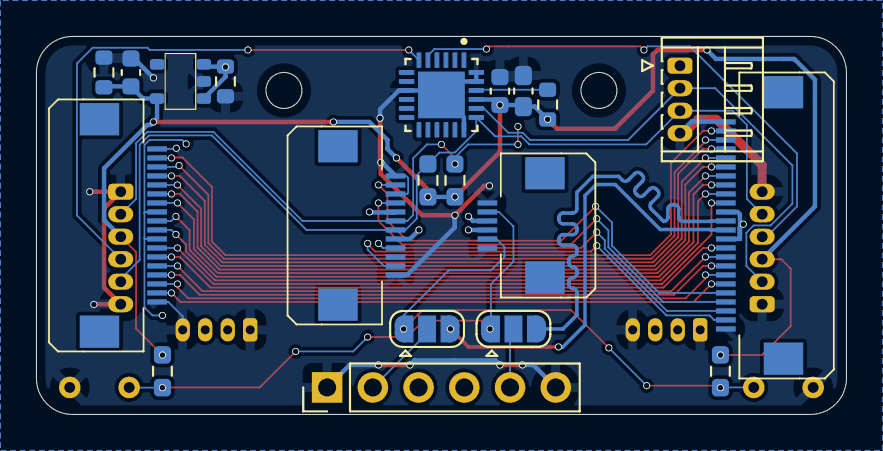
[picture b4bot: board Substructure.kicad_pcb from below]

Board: 2 copper layers, 45.0 x 21.0 mm, 26 parts (20 on the bottom side), 32 nets.

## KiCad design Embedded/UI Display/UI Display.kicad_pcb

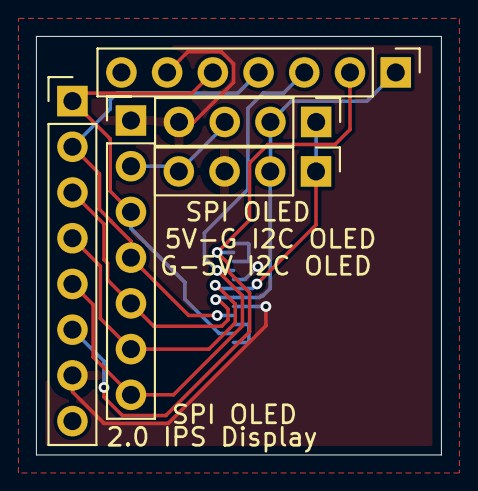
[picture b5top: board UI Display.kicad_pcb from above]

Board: 2 copper layers, 22.5 x 23.2 mm, 6 parts (1 on the bottom side), 8 nets.

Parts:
J1: 2.0 IPS Display; PinHeader_1x08_P2.54mm_Vertical
J2, J5: SPI OLED; PinHeader_1x07_P2.54mm_Vertical
J3: 5V-G I2C OLED; PinHeader_1x04_P2.54mm_Vertical
J4: G-5V I2C OLED; PinHeader_1x04_P2.54mm_Vertical
U2: FFC [U]; FFC Aliexpress 0.5mm 12P

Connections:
+5V: J1.7, J2.1, J3.4, J4.3, J5.6, U2.5, U2.8
GND: J1.8, J2.2, J3.3, J4.4, J5.7, U2.1, U2.3, U2.10, U2.12
UI 0: J1.1, J2.3, J5.5, U2.2
UI 1: J1.2, J2.4, J5.4, U2.4
UI 2: J1.5, J2.7, J5.3, U2.9
UI 3: J1.6, J5.2, U2.11
UI IO 0: J1.3, J2.5, J3.2, J4.2, J5.1, U2.6
UI IO 1: J1.4, J2.6, J3.1, J4.1, U2.7
